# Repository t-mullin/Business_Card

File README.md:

# STG Business Card

## UPDATE!  
I am working on some updates to the STG Business Card project.
1. Adding additional options of form-factor/materials.
2. Adding Through-Hole and SMD versions.
3. Reworking of the project structure.

## Motive
The motive behind this project is to provide to prospective employers an example of my pcb work in a form factor that is easy for them to carry around. I came up with the idea of putting a simple Stepped Tone Generator onto a PCB the size of a business card after watching a video from [Look Mum No Computer](https://www.youtube.com/watch?v=4lK7kdgK7dI), where he builds an Atari Punk Console (Stepped Tone Generator). 

## PCB Design
Using the same instructables guide from [BrownDogGadgets](https://www.instructables.com/Build-an-Atari-Punk-circuit-on-a-breadboard/), I used KiCad to draw up the schematic and designed a PCB to go with it. The PCB is a 2-layer design with through-hole components. Below are pictures of the 3D model and the PCB layout in KiCad.   

## Bill of Materials
| Description      | Ref      | Component Value | Part #            | Link                                                                                                        |
| ---------------- | -------- | --------------- | ----------------- | ----------------------------------------------------------------------------------------------------------- |
| Resistor         | R1       | 1K              | CFR-25JB-52-1K    | [Digi-key](https://www.digikey.com/en/products/detail/yageo/CFR-25JB-52-1K/96)                              |
| Capacitor        | C1, C2   | 0.22u           | K224M20X7RF53H5 | [Mouser](https://www.mouser.com/ProductDetail/Vishay-BC-Components/K224M20X7RF53H5?qs=ODefv%2FJbNkjoPr%252Bz4Qq7xw%3D%3D)            |
| 556 Timer        | U1       | 556             | NE556N            | [Mouser](https://www.mouser.com/ProductDetail/Texas-Instruments/NE556N?qs=gb35HGp1gQKUkn%252B6zgU6RA%3D%3D) |
| IC Socket        | U1       | 14 Pin DIP      | ICS-314-T         | [Digi-Key](https://www.digikey.com/en/products/detail/adam-tech/ICS-314-T/9832866)
| Photoresistor    | PR1, PR2 | 1k - 10k        | 161               | [Adafruit](https://www.adafruit.com/product/161)                                                            |
| Trimmer Resistor | TR1      | 5k              | 3386T             | [Mouser](https://www.mouser.com/ProductDetail/Bourns/3386T-1-502LF?qs=0VqvB9JLnIv4eQGVkebFKQ%3D%3D)         | 
| Speaker          | LS1      | 8 ohm           | 1890              | [Adafruit](https://www.adafruit.com/product/1890)                                                           |
| Switch           | SW1      | SPDT            | 805               | [Adafruit](https://www.adafruit.com/product/805)                                                            |
| 9V Battery Clip  | Batt/9V  | 9V              | 235               | [Mouser](https://www.mouser.com/ProductDetail/Keystone-Electronics/235?qs=w4ABFRoM%2FL90W35cnqrFmA%3D%3D)   |

## Assembly Order
For ease of assembly, start with the lower profile components and work up to the higher profile components.

I assembled the circuit in this order: 
1. Resistor and Photoresistors 
2. IC Socket
3. Capacitors
4. Switch
5. Potentiometer
6. Speaker and Battery Clip
7. IC

## Assembled Circuit
Below is an assembled STG circuit. A demo of the circuit can be found here: [STG Demo](https://youtu.be/Ry3vZIr_BqI)

## Postmortem
Overall, I happy with the final product. ~~However, I may add an additional PCB, to this project, that swaps out the photoresistors for potentiometers.~~ Alternate version has been added. However, it is untested.
For the alternate design, below are the parts that have changed.
- TR2 & TR3 = 500k ohms
- C1 & C2 = 0.01 uF

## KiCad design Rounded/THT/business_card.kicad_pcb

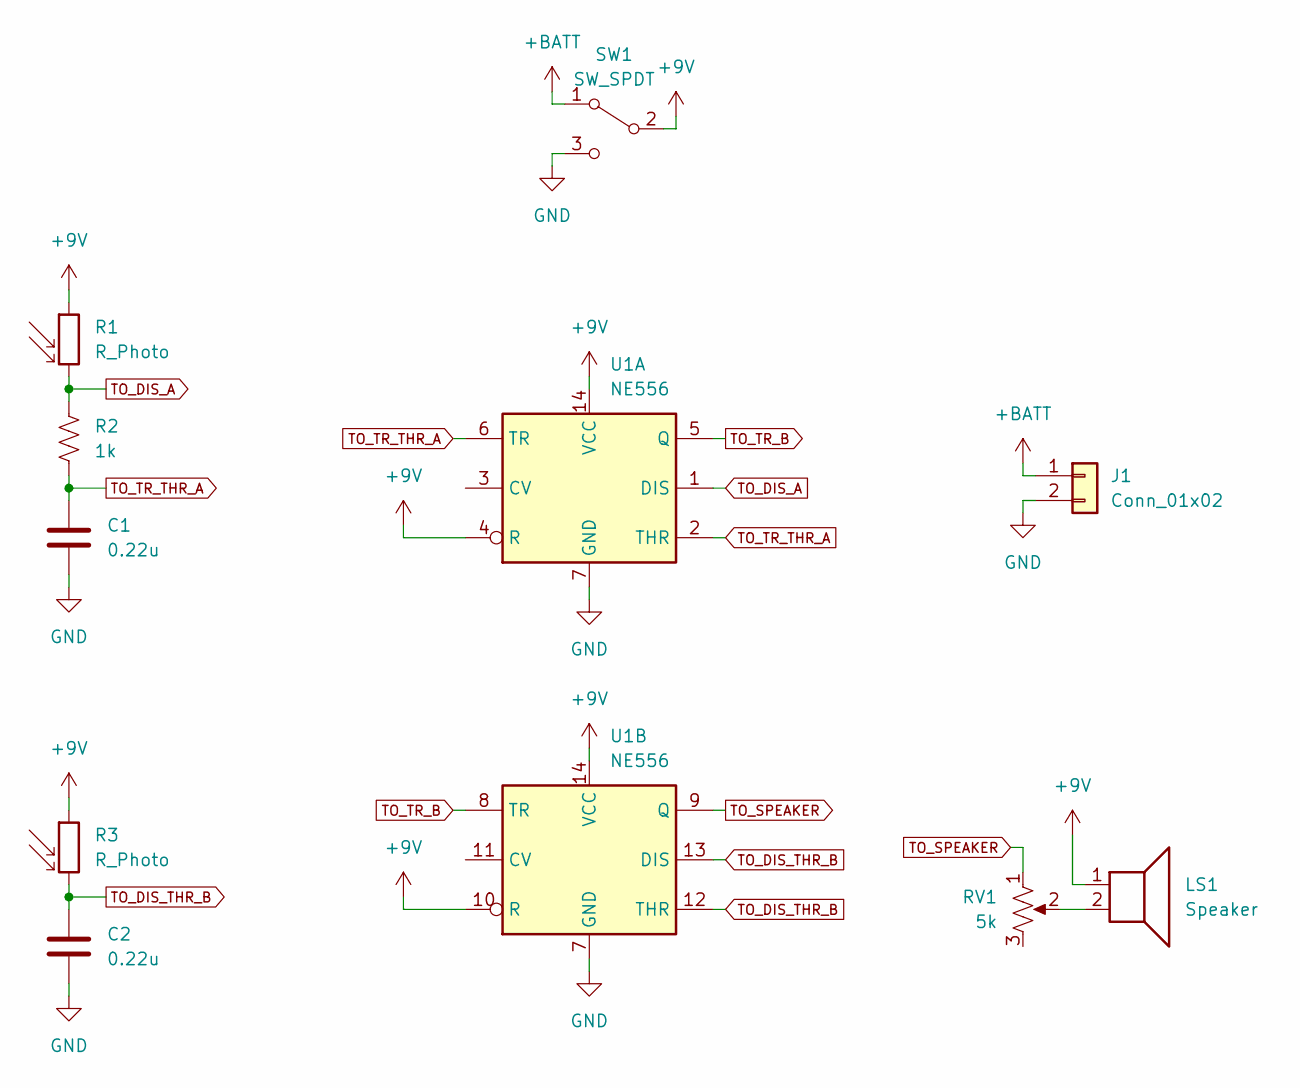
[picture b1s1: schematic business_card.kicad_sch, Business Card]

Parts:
C1, C2: 0.22u; C_Disc_D7.0mm_W2.5mm_P5.00mm
J1: Conn_01x02; PinSocket_1x02_P2.54mm_Vertical
LS1: Speaker; PinSocket_1x02_P2.54mm_Vertical
R1, R3: R_Photo; R_Axial_DIN0207_L6.3mm_D2.5mm_P5.08mm_Vertical
R2: 1k; R_Axial_DIN0207_L6.3mm_D2.5mm_P7.62mm_Horizontal
RV1: 5k; Potentiometer_Bourns_3386C_Horizontal
SW1: SW_SPDT; PinSocket_1x03_P2.54mm_Vertical
U1: NE556; DIP-14_W7.62mm_Socket_LongPads

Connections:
+9V: LS1.1, R1.1, R3.1, SW1.2 (B), U1.4 (R), U1.10 (R), U1.14 (VCC)
+BATT: J1.1, SW1.1 (A)
GND: C1.2, C2.2, J1.2, SW1.3 (C), U1.7 (GND)
unnamed: LS1.2, RV1.2
TO_DIS_A: R1.2, R2.1, U1.1 (DIS)
TO_DIS_THR_B: C2.1, R3.2, U1.12 (THR), U1.13 (DIS)
TO_SPEAKER: RV1.1, U1.9 (Q)
TO_TR_B: U1.5 (Q), U1.8 (TR)
TO_TR_THR_A: C1.1, R2.2, U1.2 (THR), U1.6 (TR)

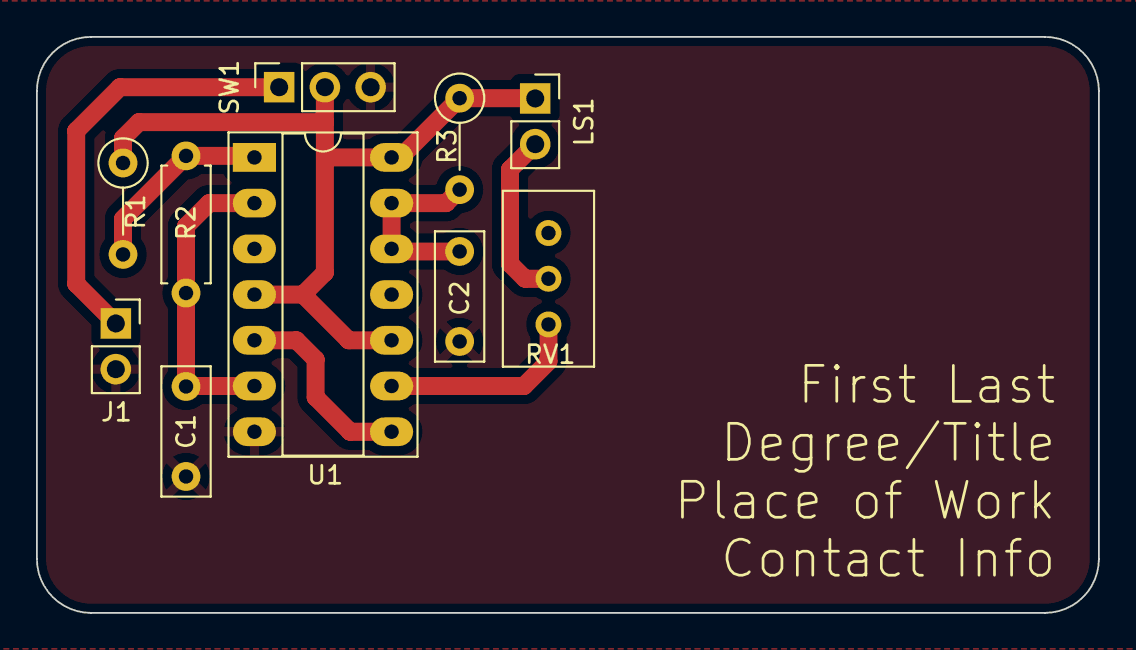
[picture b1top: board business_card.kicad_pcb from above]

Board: 2 copper layers, 59.0 x 32.0 mm, 10 parts (0 on the bottom side), 9 nets.

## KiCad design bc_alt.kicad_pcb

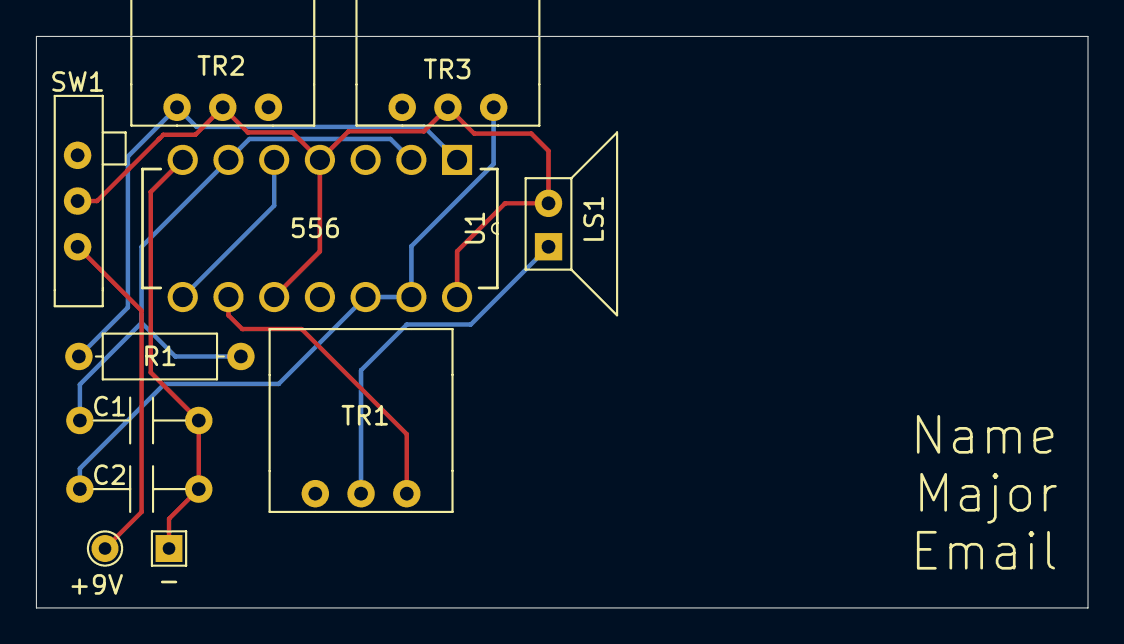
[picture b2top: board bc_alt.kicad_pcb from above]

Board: 2 copper layers, 58.4 x 31.8 mm, 11 parts (0 on the bottom side), 8 nets.

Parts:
+9V: TestPoint_THTPad_D1.5mm_Drill0.7mm
-: TestPoint_THTPad_1.5x1.5mm_Drill0.7mm
C1, C2: c_gen
LS1: Speaker; speaker_gen
R1: r_gen
SW1: slide_switch_general
TR1, TR2, TR3: trimpot_gen
U1: NE556N_gen; DIP254P762X508-14

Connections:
+BATT: +9V.1, LS1.1, SW1.2, SW1.3, TR2.2, TR3.2, U1.4, U1.10, U1.14
GND: -.1, C1.2, C2.2, U1.7
unnamed: C1.1, R1.2, U1.2, U1.6
unnamed: C2.1, TR3.3, U1.12, U1.13
unnamed: LS1.2, TR1.2
unnamed: R1.1, TR2.1, U1.1
unnamed: TR1.3, U1.9
unnamed: U1.5, U1.8

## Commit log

2021-06-22 setting up repo
2021-06-22 Added Bill of Materials to the README.
2021-06-22 Updated README with the motive behind the project.
2021-06-22 added KiCad project files
2021-06-22 added image to README
2021-06-22 added image to README and moved battery silkscreen lables
2021-06-22 modified the qr code url
2021-07-06 Switched out Capacitor part and supplier.
2021-07-06 changed out the traces img
2021-07-06 fixed unintended wrapping in the BOM table
2021-07-12 added image of a completed stg
2021-07-12 Added additional information to the README.
2021-07-12 Fixed a typo
2021-07-13 Added youtube link for stg demo
2021-07-13 added alt version that has trim pots instead of photoresistors
2022-08-23 major reorg
2022-08-23 added note to README
2022-08-23 added a rounded corners version
